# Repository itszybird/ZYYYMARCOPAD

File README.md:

# ZYYYMARCOPAD
a marco pad for templating a actually keyboard

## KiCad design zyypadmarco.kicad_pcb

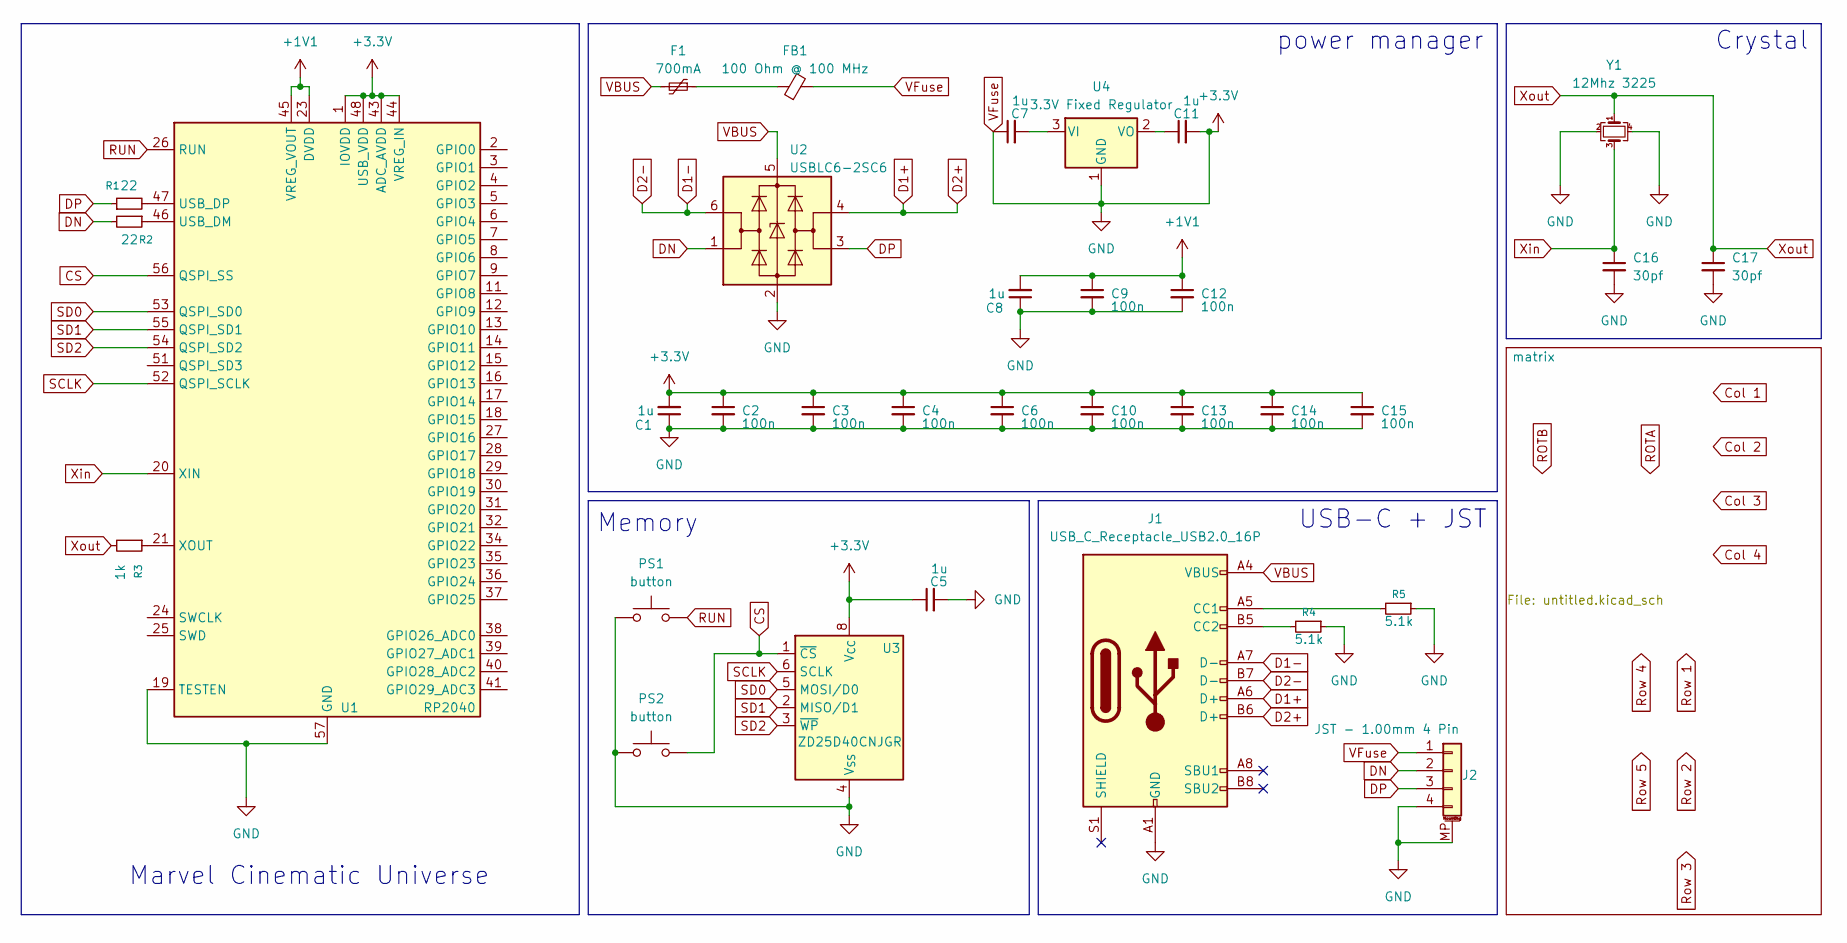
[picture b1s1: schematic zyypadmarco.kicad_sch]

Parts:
C1, C5, C7, C8, C11: 1u; C_0402_1005Metric; LCSC C52923
C2, C3, C4, C6, C9, C10, C12, C13, C14, C15: 100n; C_0402_1005Metric; LCSC C1525
C16, C17: 30pf; C_0402_1005Metric
F1: 700mA; Fuse_0402_1005Metric; LCSC C914086
FB1: 100 Ohm @ 100 MHz; L_0402_1005Metric; LCSC C85812
J1: USB_C_Receptacle_USB2.0_16P; USB_C_Receptacle_GCT_USB4110
J2: JST - 1.00mm 4 Pin; JST_SH_SM04B-SRSS-TB_1x04-1MP_P1.00mm_Horizontal; LCSC C160404
PS1, PS2: button; SW_Push_1P1T_NO_E-Switch_TL3301NxxxxxG
R1, R2: 22; R_0805_2012Metric
R3: 1k; R_0805_2012Metric
R4, R5: 5.1k; R_0805_2012Metric
U1: RP2040; QFN-56-1EP_7x7mm_P0.4mm_EP3.2x3.2mm
U2: USBLC6-2SC6; SOT-23-6; LCSC C558442
U3: ZD25D40CNJGR; USON-8_1.5x1.5mm_P0.45mm; LCSC C3646778
U4: 3.3V Fixed Regulator; TSOT-23; LCSC C150715
Y1: 12Mhz 3225; Crystal_SMD_3225-4Pin_3.2x2.5mm_HandSoldering

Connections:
+1V1: C8.2, C9.1, C12.1, U1.23 (DVDD), U1.45 (VREG_VOUT), U1.50 (DVDD)
CS: PS2.2, U1.56 (QSPI_SS), U3.1 (~CS)
D1+: J1.A6 (D+), J1.B6 (D+), U2.4 (I/O2)
D1-: J1.A7 (D-), J1.B7 (D-), U2.6 (I/O1)
DN: J2.2, R2.2, U2.1 (I/O1)
DP: J2.3, R1.1, U2.3 (I/O2)
unnamed: F1.1, FB1.1
unnamed: J1.A5 (CC1), R5.2
unnamed: J1.B5 (CC2), R4.2
unnamed: R2.1, U1.46 (USB_DM)
unnamed: R1.2, U1.47 (USB_DP)
unnamed: R3.1, U1.21 (XOUT)
unnamed: C7.2, U4.3 (VI)
unnamed: C11.1, U4.2 (VO)
RUN: PS1.2, U1.26 (RUN)
SCLK: U1.52 (QSPI_SCLK), U3.6 (SCLK)
SD0: U1.53 (QSPI_SD0), U3.5 (MOSI/D0)
SD1: U1.55 (QSPI_SD1), U3.2 (MISO/D1)
SD2: U1.54 (QSPI_SD2), U3.3 (~WP)
VBUS: F1.2, J1.A4 (VBUS), J1.A9 (VBUS), J1.B4 (VBUS), J1.B9 (VBUS), U2.5 (VBUS)
VFuse: C1.1, C1.2, C2.1, C2.2, C3.1, C3.2, C4.1, C4.2, C5.1, C5.2, C6.1, C6.2, C7.1, C8.1, C9.2, C10.1, C10.2, C11.2, C12.2, C13.1, C13.2, C14.1, C14.2, C15.1, C15.2, C16.2, C17.2, FB1.2, J1.A1 (GND), J1.A12 (GND), J1.B1 (GND), J1.B12 (GND), J2.1, J2.4, J2.MP (MountPin), PS1.1, PS2.1, R4.1, R5.1, U1.1 (IOVDD), U1.10 (IOVDD), U1.19 (TESTEN), U1.22 (IOVDD), U1.33 (IOVDD), U1.42 (IOVDD), U1.43 (ADC_AVDD), U1.44 (VREG_IN), U1.48 (USB_VDD), U1.49 (IOVDD), U1.57 (GND), U2.2 (GND), U3.4 (V_{SS}), U3.8 (V_{CC}), U3.9 (PAD/V_{SS}), U4.1 (GND), Y1.2, Y1.4; also elsewhere on the board
Xin: C16.1, U1.20 (XIN), Y1.3
Xout: C17.1, R3.2, Y1.1

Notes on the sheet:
Memory
Marvel Cinematic Universe
power manager
USB-C + JST
Crystal

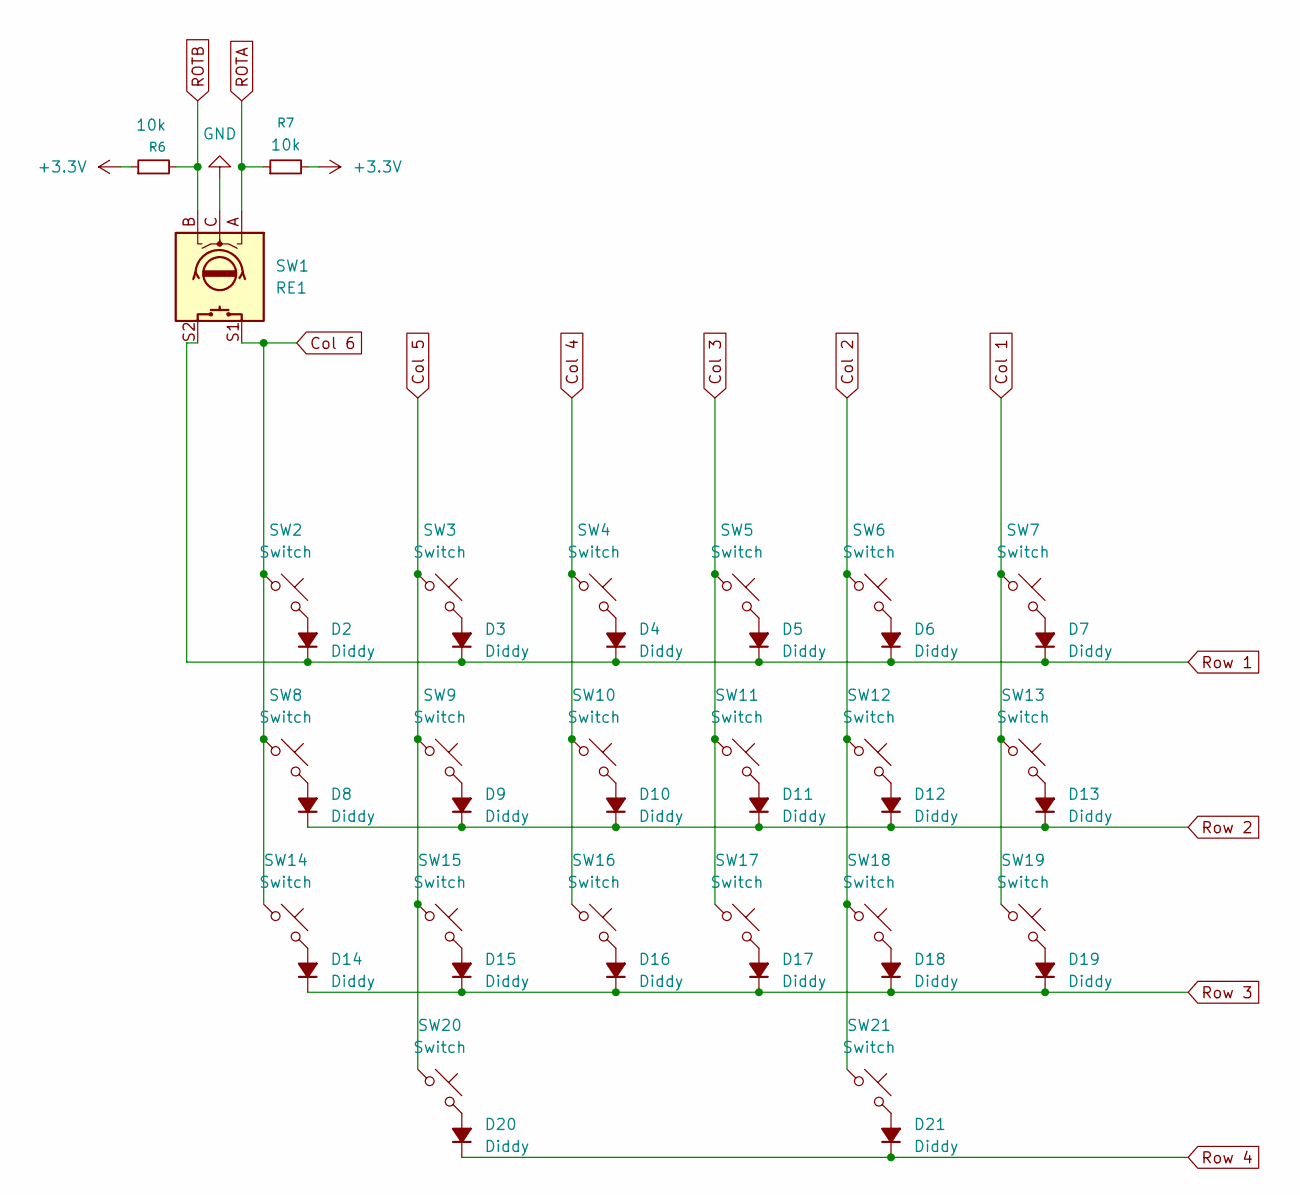
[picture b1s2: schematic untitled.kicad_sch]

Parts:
D2, D3, D4, D5, D6, D7, D8, D9, D10, D11, D12, D13, D14, D15, D16, D17, D18, D19, D20, D21: Diddy; D_SOD-123
R6, R7: 10k; R_0805_2012Metric
SW1: RE1; ROT_Alps_EC11E-Switch
SW2, SW3, SW4, SW5, SW6, SW7, SW8, SW9, SW10, SW11, SW12, SW13, SW14, SW15, SW16, SW17, SW18, SW19, SW20, SW21: Switch; SW_MX_HS_CPG151101S11_1u

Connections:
Col 1: SW7.1, SW13.1, SW19.1
Col 2: SW6.1, SW12.1, SW18.1, SW21.1
Col 3: SW5.1, SW11.1, SW17.1
Col 4: SW4.1, SW10.1, SW16.1
Col 5: SW3.1, SW9.1, SW15.1, SW20.1
Col 6: SW1.S1, SW2.1, SW8.1, SW14.1
unnamed: D2.2 (A), SW2.2
unnamed: D3.2 (A), SW3.2
unnamed: D4.2 (A), SW4.2
unnamed: D5.2 (A), SW5.2
unnamed: D6.2 (A), SW6.2
unnamed: D7.2 (A), SW7.2
unnamed: D8.2 (A), SW8.2
unnamed: D9.2 (A), SW9.2
unnamed: D10.2 (A), SW10.2
unnamed: D11.2 (A), SW11.2
unnamed: D12.2 (A), SW12.2
unnamed: D13.2 (A), SW13.2
unnamed: D14.2 (A), SW14.2
unnamed: D15.2 (A), SW15.2
unnamed: D16.2 (A), SW16.2
unnamed: D17.2 (A), SW17.2
unnamed: D18.2 (A), SW18.2
unnamed: D19.2 (A), SW19.2
unnamed: D20.2 (A), SW20.2
unnamed: D21.2 (A), SW21.2
ROTA: R7.1, SW1.A
ROTB: R6.2, SW1.B
Row 1: D2.1 (K), D3.1 (K), D4.1 (K), D5.1 (K), D6.1 (K), D7.1 (K), SW1.S2
Row 2: D8.1 (K), D9.1 (K), D10.1 (K), D11.1 (K), D12.1 (K), D13.1 (K)
Row 3: D14.1 (K), D15.1 (K), D16.1 (K), D17.1 (K), D18.1 (K), D19.1 (K)
Row 4: D20.1 (K), D21.1 (K)
VFuse: R6.1, R7.2, SW1.C; also elsewhere on the board

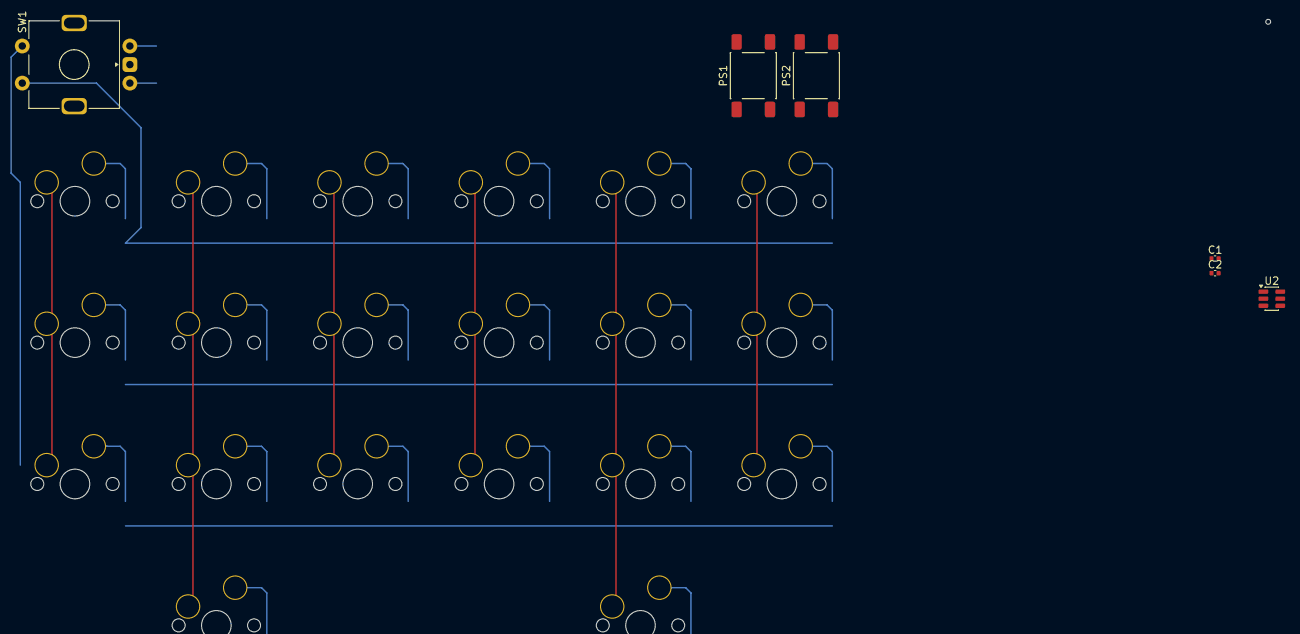
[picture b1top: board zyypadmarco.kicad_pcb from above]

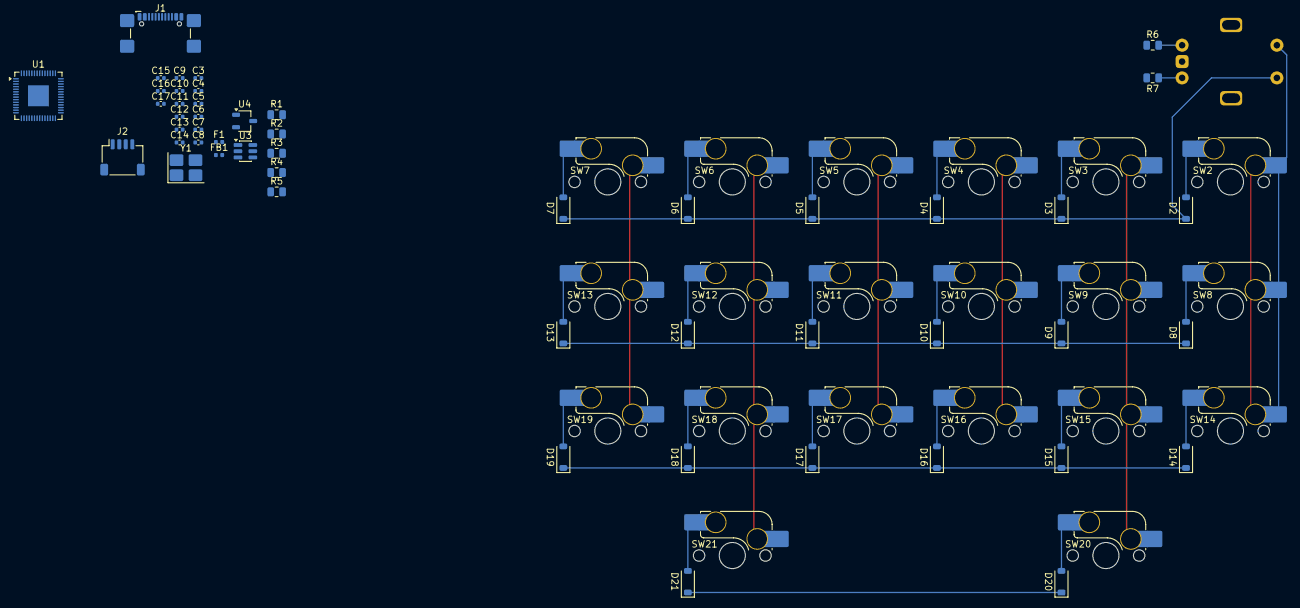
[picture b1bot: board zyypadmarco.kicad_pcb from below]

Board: 2 copper layers, 76 parts (70 on the bottom side), 55 nets.

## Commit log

2025-12-31 schematic
